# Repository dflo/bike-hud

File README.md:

# bike-hud
HUD for motorcycle helmets

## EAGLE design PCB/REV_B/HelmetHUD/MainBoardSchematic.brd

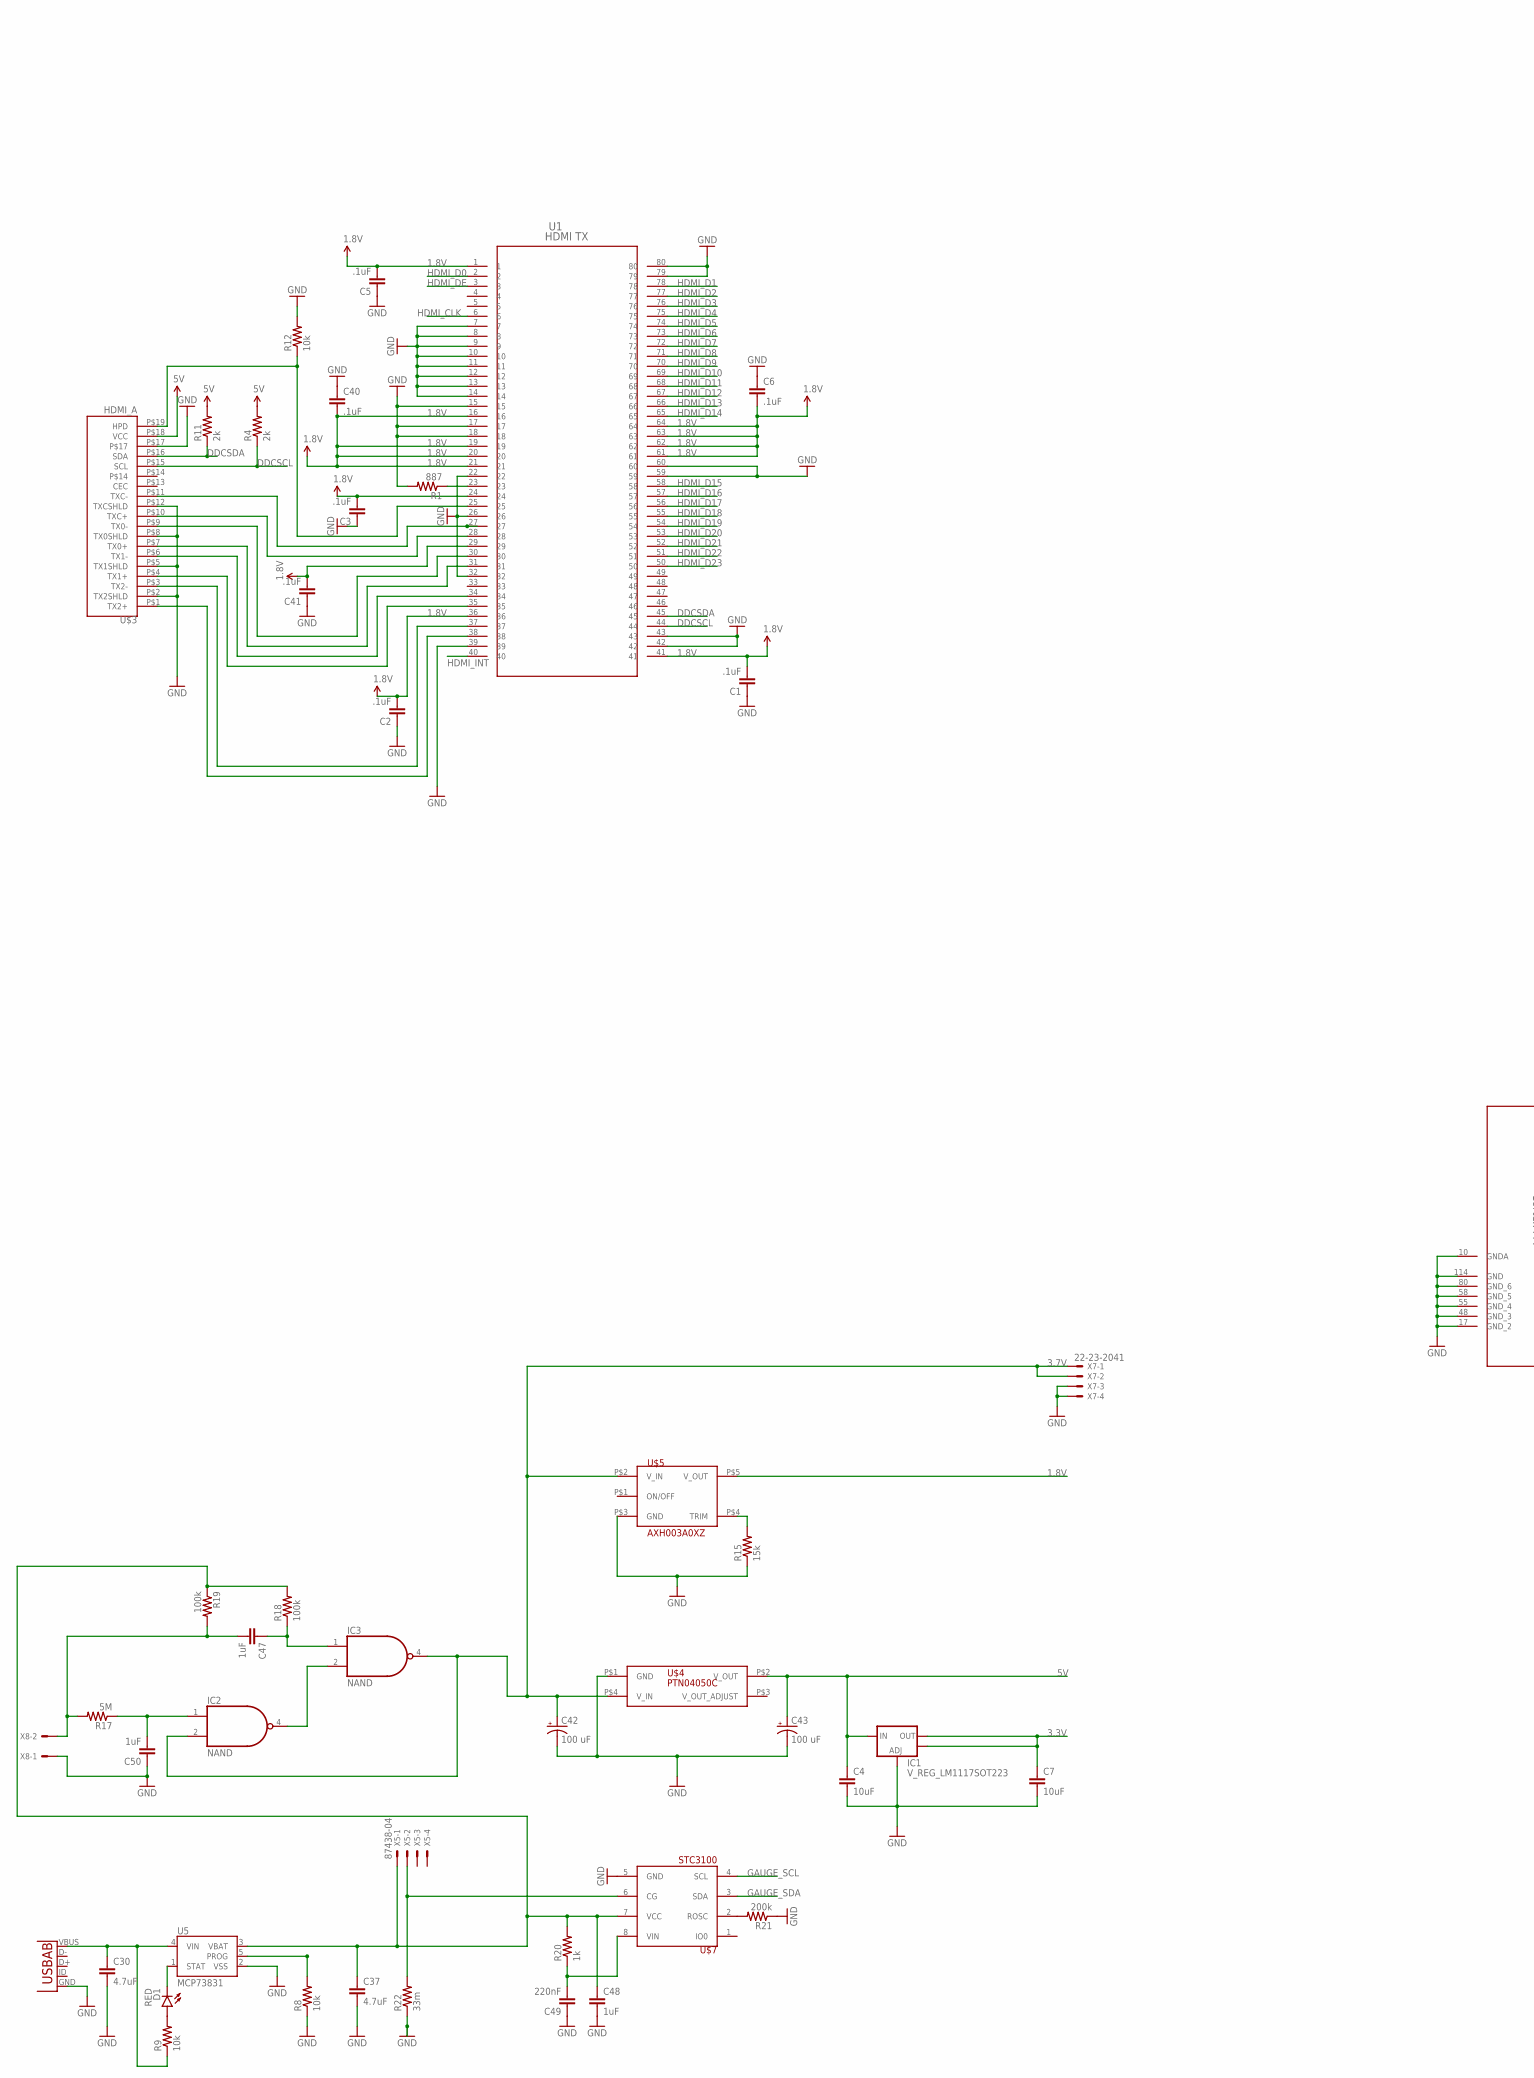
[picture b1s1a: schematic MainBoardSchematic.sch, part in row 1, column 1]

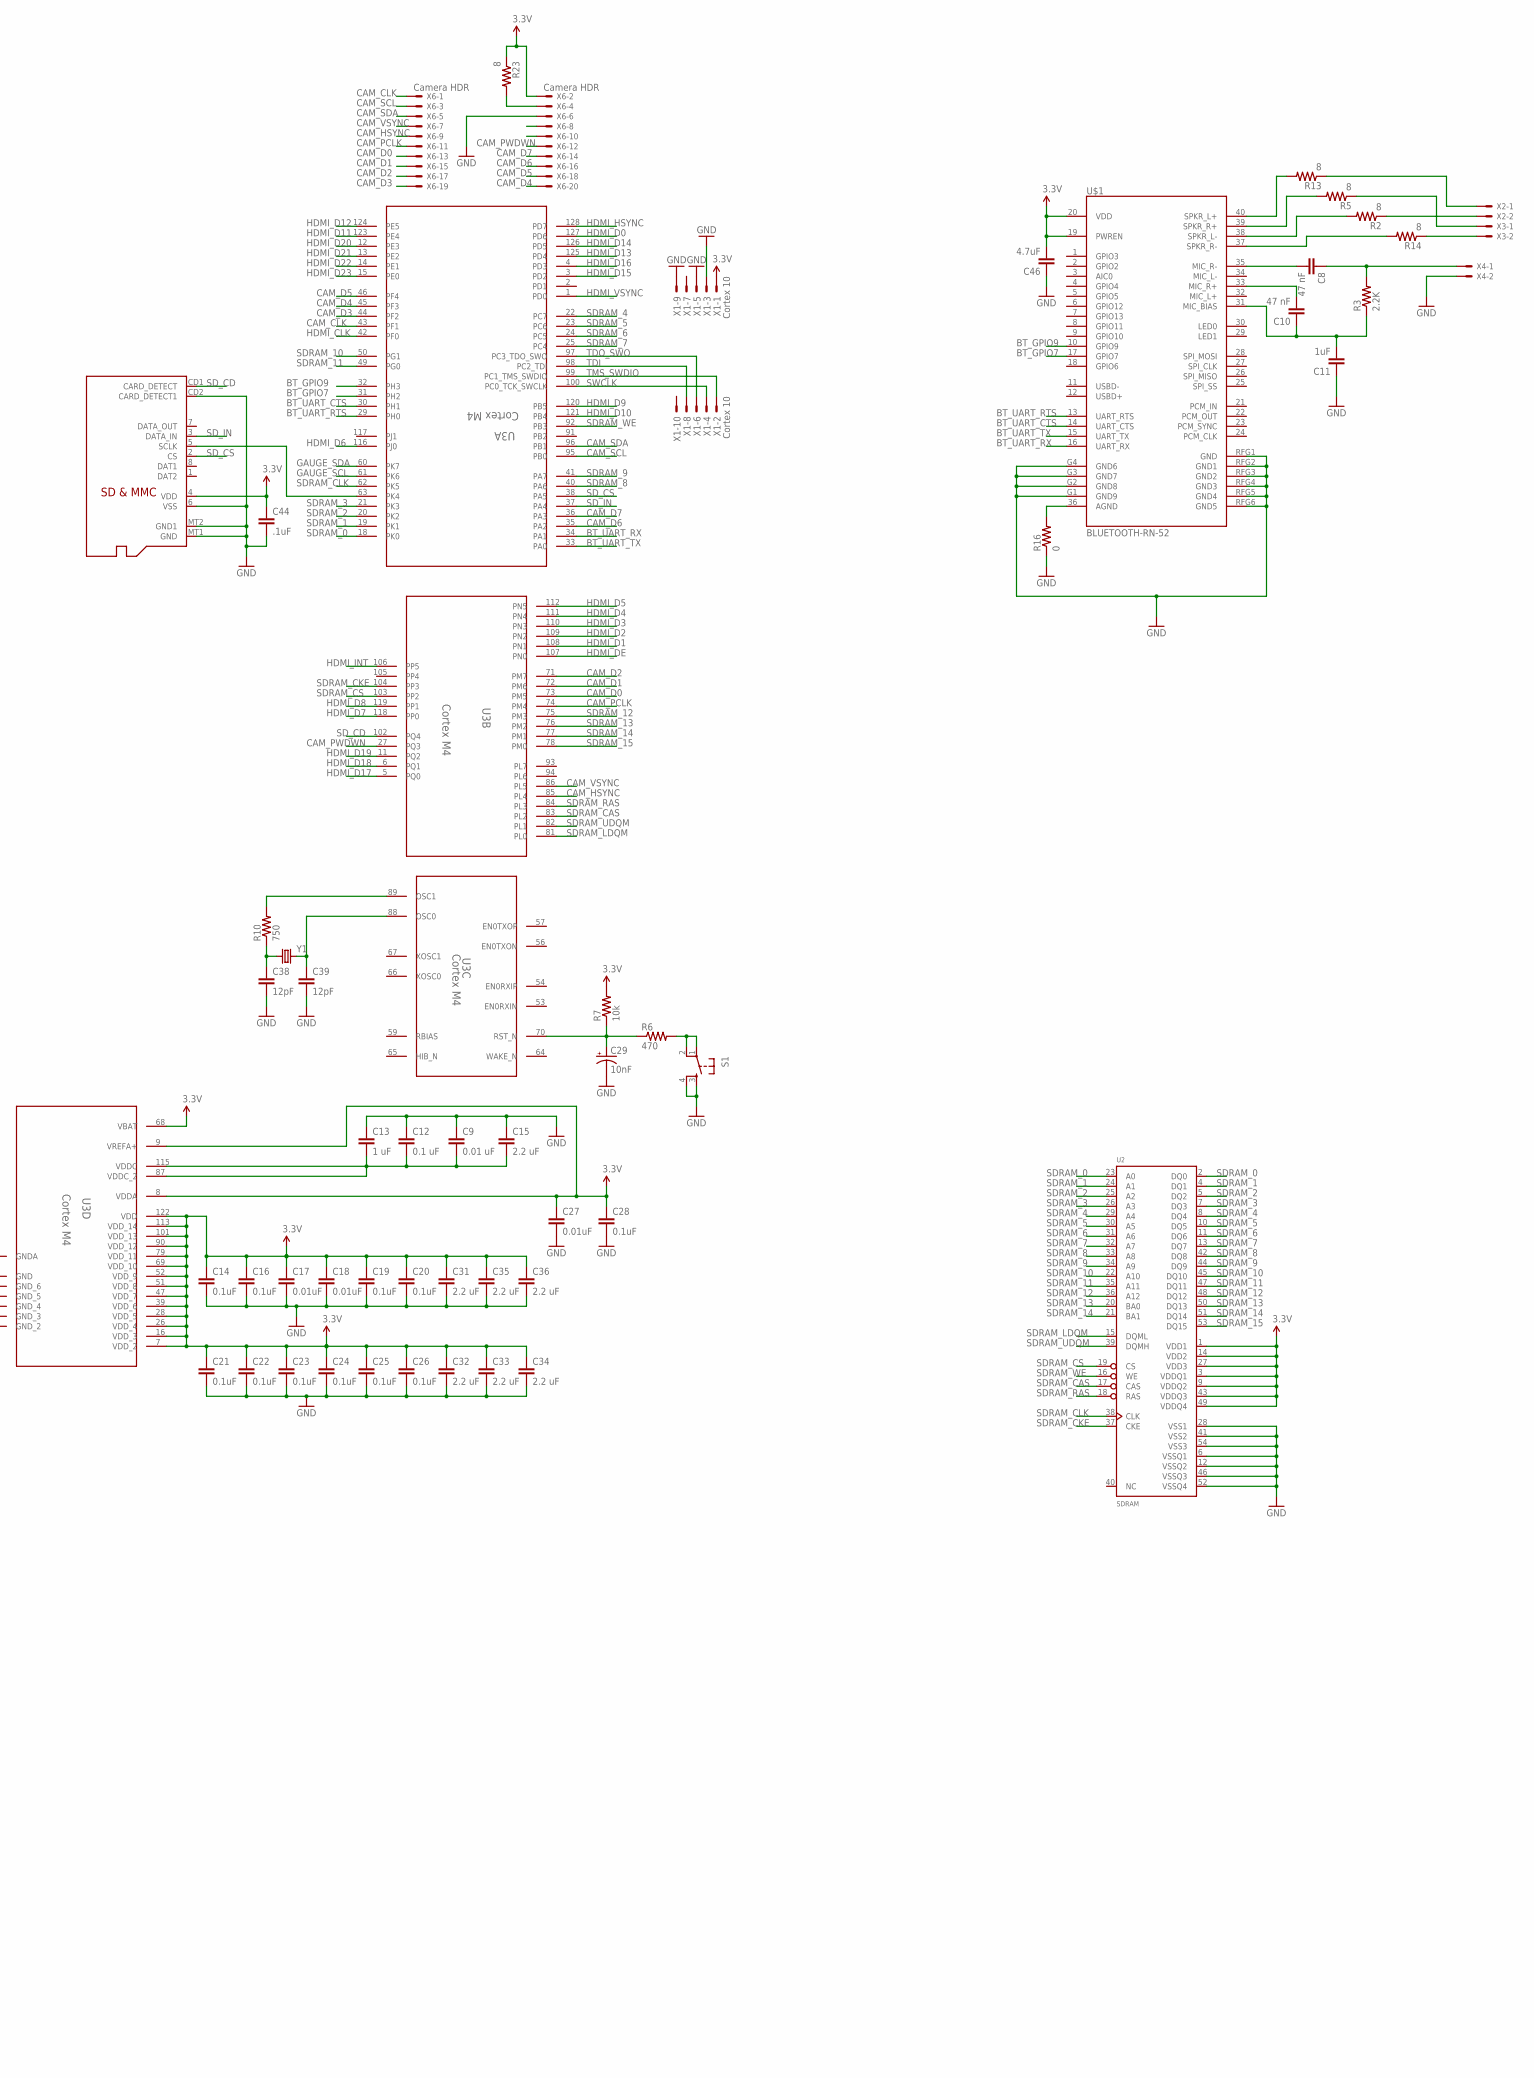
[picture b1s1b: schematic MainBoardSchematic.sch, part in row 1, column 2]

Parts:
C1, C2, C3, C5, C6, C40, C41, C44: .1uF; 0603-CAP
C4, C7: 10uF; 0603-CAP
C8, C10: 47 nF; 0603-CAP
C9: 0.01 uF; 0603-CAP
C11, C47, C48, C50: 1uF; 0603-CAP
C12: 0.1 uF; 0603-CAP
C13: 1 uF; 0603-CAP
C14, C16, C19, C20, C21, C22, C23, C24, C25, C26, C28: 0.1uF; 0603-CAP
C15, C31, C32, C33, C34, C35, C36: 2.2 uF; 0603-CAP
C17, C18, C27: 0.01uF; 0603-CAP
C29: 10nF; EIA6032
C30, C37, C46: 4.7uF; 0603-CAP
C38, C39: 12pF; 0603-CAP
C42, C43: 100 uF; EIA6032
C49: 220nF; 0603-CAP
D1: RED; LED-0603
IC1: V_REG_LM1117SOT223; SOT223
IC2, IC3: NAND; SOT23-5
R1: 887; 0603-RES
R2, R5, R13, R14, R23: 8; 1206
R3: 2.2K; 1206
R4, R11: 2k; 0603-RES
R6: 470; 0603-RES
R7, R8, R9, R12: 10k; 0603-RES
R10: 750; 0603-RES
R15: 15k; 0603-RES
R16: 0; 1206
R17: 5M; 0603-RES
R18, R19: 100k; 0603-RES
R20: 1k; 0603-RES
R21: 200k; 0603-RES
R22: 33m; 0603-RES
S1: TAC_SWITCHPTH; TACTILE-PTH
U1: HDMI TX; ST_80_2
U2: SDRAM; TSOP54-400
U3: Cortex M4; PDT0128A_N
U4: USB-AB; USB-AB-MICRO-SMD
U5: MCP73831; SOT23-5
U$1: BLUETOOTH-RN-52; RN-52
U$2: MICROSD
U$3: HDMI_A; HDMI_A_SMD
U$4: PTN04050C
U$5: AXH003A0XZ
U$7: STC3100; MSOP8
X1: Cortex 10; 1365-10
X2, X3, X4, X8: KK-156-2
X5: 87438-04
X6: Camera HDR; 87758-2016
X7: 22-23-2041
Y1: CRYSTAL; NX5032GA

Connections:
1.8V: C1.2, C2.2, C3.2, C5.2, C6.2, C40.2, C41.2, U1.1, U1.16, U1.19, U1.20, U1.21, U1.24, U1.29, U1.36, U1.41, U1.61, U1.62, U1.63, U1.64, U$5.P$5 (V_OUT)
3.3V: C7.1, C14.1, C16.1, C17.1, C18.1, C19.1, C20.1, C21.1, C22.1, C23.1, C24.1, C25.1, C26.1, C27.1, C28.1, C31.1, C32.1, C33.1, C34.1, C35.1, C36.1, C44.1, C46.2, IC1.2 (OUT), IC1.4 (OUT), R7.2, R23.1, U2.1 (VDD1), U2.3 (VDDQ1), U2.9 (VDDQ2), U2.14 (VDD2), U2.27 (VDD3), U2.43 (VDDQ3), U2.49 (VDDQ4), U3.7 (VDD_2), U3.8 (VDDA), U3.9 (VREFA+), U3.16 (VDD_3), U3.26 (VDD_4), U3.28 (VDD_5), U3.39 (VDD_6), U3.47 (VDD_7), U3.51 (VDD_8), U3.52 (VDD_9), U3.68 (VBAT), U3.69 (VDD_10), U3.79 (VDD_11), U3.90 (VDD_12), U3.101 (VDD_13), U3.113 (VDD_14), U3.122 (VDD), U$1.19 (PWREN), U$1.20 (VDD), U$2.4 (VDD), X1.1, X6.2
3.7V: C42.P$1 (+), IC2.2 (I1), IC3.4 (O), U$4.P$4 (V_IN), U$5.P$2 (V_IN), X7.1, X7.2
5V: C4.1, C43.P$1 (+), IC1.3 (IN), R4.2, R11.2, U$3.P$18 (VCC), U$4.P$2 (V_OUT)
BT_GPIO7: U3.31 (PH2), U$1.17 (GPIO7)
BT_GPIO9: U3.32 (PH3), U$1.10 (GPIO9)
BT_UART_CTS: U3.30 (PH1), U$1.14 (UART_CTS)
BT_UART_RTS: U3.29 (PH0), U$1.13 (UART_RTS)
BT_UART_RX: U3.34 (PA1), U$1.16 (UART_RX)
BT_UART_TX: U3.33 (PA0), U$1.15 (UART_TX)
CAM_CLK: U3.43 (PF1), X6.1
CAM_D0: U3.73 (PM5), X6.13
CAM_D1: U3.72 (PM6), X6.15
CAM_D2: U3.71 (PM7), X6.17
CAM_D3: U3.44 (PF2), X6.19
CAM_D4: U3.45 (PF3), X6.20
CAM_D5: U3.46 (PF4), X6.18
CAM_D6: U3.35 (PA2), X6.16
CAM_D7: U3.36 (PA3), X6.14
CAM_HSYNC: U3.85 (PL4), X6.9
CAM_PCLK: U3.74 (PM4), X6.11
CAM_PWDWN: U3.27 (PQ3), X6.12
CAM_SCL: U3.95 (PB0), X6.3
CAM_SDA: U3.96 (PB1), X6.5
CAM_VSYNC: U3.86 (PL5), X6.7
DDCSCL: R4.1, U1.44, U$3.P$15 (SCL)
DDCSDA: R11.1, U1.45, U$3.P$16 (SDA)
GAUGE_SCL: U3.61 (PK6), U$7.4 (SCL)
GAUGE_SDA: U3.60 (PK7), U$7.3 (SDA)
GND: C1.1, C2.1, C3.1, C4.2, C5.1, C6.1, C7.2, C9.1, C11.1, C12.1, C13.1, C14.2, C15.1, C16.2, C17.2, C18.2, C19.2, C20.2, C21.2, C22.2, C23.2, C24.2, C25.2, C26.2, C27.2, C28.2, C29.P$2 (-), C30.2, C31.2, C32.2, C33.2, C34.2, C35.2, C36.2, C37.2, C38.2, C39.2, C40.1, C41.1, C42.P$2 (-), C43.P$2 (-), C44.2, C46.1, C48.2, C49.1, C50.1, IC1.1 (ADJ), IC2.3 (GND), IC3.3 (GND), R1.2, R8.1, R12.2, R15.1, R16.1, R21.1, R22.1, S1.3, S1.4, U1.7, U1.8, U1.9, U1.10, U1.11, U1.12, U1.13, U1.14, U1.15, U1.17, U1.18, U1.22, U1.26, U1.32, U1.39, U1.42, U1.43, U1.59, U1.60, U1.79, U1.80, U2.6 (VSSQ1), U2.12 (VSSQ2), U2.28 (VSS1), U2.41 (VSS2), U2.46 (VSSQ3), U2.52 (VSSQ4), U2.54 (VSS3), U3.10 (GNDA), U3.17 (GND_2), U3.48 (GND_3), U3.55 (GND_4), U3.58 (GND_5), U3.80 (GND_6), U3.114 (GND), U4.GND, U5.2 (VSS), U$1.G1 (GND9), U$1.G2 (GND8), U$1.G3 (GND7), U$1.G4 (GND6), U$1.RFG1 (GND), U$1.RFG2 (GND1), U$1.RFG3 (GND2), U$1.RFG4 (GND3), U$1.RFG5 (GND4), U$1.RFG6 (GND5), U$2.6 (VSS), U$2.CD2 (CARD_DETECT1), U$2.MT1 (GND), U$2.MT2 (GND1), U$3.P$2 (TX2SHLD), U$3.P$5 (TX1SHLD), U$3.P$8 (TX0SHLD), U$3.P$12 (TXCSHLD), U$3.P$17, U$4.P$1 (GND), U$5.P$3 (GND), U$7.5 (GND), X1.3, X1.5, X1.9, X4.2, X6.6, X7.3, X7.4, X8.1
HDMI_CLK: U1.6, U3.42 (PF0)
HDMI_D0: U1.2, U3.127 (PD6)
HDMI_D1: U1.78, U3.108 (PN1)
HDMI_D2: U1.77, U3.109 (PN2)
HDMI_D3: U1.76, U3.110 (PN3)
HDMI_D4: U1.75, U3.111 (PN4)
HDMI_D5: U1.74, U3.112 (PN5)
HDMI_D6: U1.73, U3.116 (PJ0)
HDMI_D7: U1.72, U3.118 (PP0)
HDMI_D8: U1.71, U3.119 (PP1)
HDMI_D9: U1.70, U3.120 (PB5)
HDMI_D10: U1.69, U3.121 (PB4)
HDMI_D11: U1.68, U3.123 (PE4)
HDMI_D12: U1.67, U3.124 (PE5)
HDMI_D13: U1.66, U3.125 (PD4)
HDMI_D14: U1.65, U3.126 (PD5)
HDMI_D15: U1.58, U3.3 (PD2)
HDMI_D16: U1.57, U3.4 (PD3)
HDMI_D17: U1.56, U3.5 (PQ0)
HDMI_D18: U1.55, U3.6 (PQ1)
HDMI_D19: U1.54, U3.11 (PQ2)
HDMI_D20: U1.53, U3.12 (PE3)
HDMI_D21: U1.52, U3.13 (PE2)
HDMI_D22: U1.51, U3.14 (PE1)
HDMI_D23: U1.50, U3.15 (PE0)
HDMI_DE: U1.3, U3.107 (PN0)
HDMI_HSYNC: U3.128 (PD7)
HDMI_INT: U1.40, U3.106 (PP5)
HDMI_VSYNC: U3.1 (PD0)
unnamed: R12.1, U1.25, U$3.P$19 (HPD)
unnamed: R1.1, U1.23
unnamed: U1.34, U$3.P$6 (TX1-)
unnamed: U1.30, U$3.P$9 (TX0-)
unnamed: U1.31, U$3.P$7 (TX0+)
unnamed: U1.35, U$3.P$4 (TX1+)
unnamed: U1.37, U$3.P$3 (TX2-)
unnamed: U1.38, U$3.P$1 (TX2+)
unnamed: U1.28, U$3.P$10 (TXC+)
unnamed: C8.2, U$1.35 (MIC_R-)
unnamed: C10.1, C11.2, R3.1, U$1.31 (MIC_BIAS)
unnamed: C8.1, R3.2, X4.1
unnamed: R6.2, S1.1, S1.2
unnamed: R13.2, U$1.40 (SPKR_L+)
unnamed: R5.2, U$1.39 (SPKR_R+)
unnamed: R2.2, U$1.38 (SPKR_L-)
unnamed: R14.2, U$1.37 (SPKR_R-)
unnamed: R23.2, X6.4
unnamed: U1.27, U$3.P$11 (TXC-)
unnamed: C30.1, R9.1, U4.VBUS, U5.4 (VIN)
unnamed: R15.2, U$5.P$4 (TRIM)
unnamed: C9.2, C12.2, C13.2, C15.2, U3.87 (VDDC_2), U3.115 (VDDC)
unnamed: C29.P$1 (+), R6.1, R7.1, U3.70 (RST_N)
unnamed: C38.1, R10.1, Y1.P$1 (1)
unnamed: R8.2, U5.5 (PROG)
unnamed: C39.1, U3.88 (OSC0), Y1.P$2 (2)
unnamed: R16.2, U$1.36 (AGND)
unnamed: R10.2, U3.89 (OSC1)
unnamed: R14.1, X3.2
unnamed: R2.1, X2.2
unnamed: R5.1, X3.1
unnamed: R13.1, X2.1
unnamed: D1.A, R9.2
unnamed: D1.C, U5.1 (STAT)
unnamed: IC2.4 (O), IC3.2 (I1)
unnamed: C47.1, IC3.1 (I0), R18.1
unnamed: C47.2, R17.2, R19.2, X8.2
unnamed: C37.1, C48.1, R18.2, R19.1, R20.2, U5.3 (VBAT), U$7.7 (VCC), X5.1
unnamed: C50.2, IC2.1 (I0), R17.1
unnamed: C49.2, R20.1, U$7.8 (VIN)
unnamed: R21.2, U$7.2 (ROSC)
unnamed: R22.2, U$7.6 (CG), X5.2
unnamed: U3.63 (PK4), U$2.5 (SCLK)
unnamed: C10.2, U$1.33 (MIC_R+)
SDRAM_0: U2.2 (DQ0), U2.23 (A0), U3.18 (PK0)
SDRAM_1: U2.4 (DQ1), U2.24 (A1), U3.19 (PK1)
SDRAM_2: U2.5 (DQ2), U2.25 (A2), U3.20 (PK2)
SDRAM_3: U2.7 (DQ3), U2.26 (A3), U3.21 (PK3)
SDRAM_4: U2.8 (DQ4), U2.29 (A4), U3.22 (PC7)
SDRAM_5: U2.10 (DQ5), U2.30 (A5), U3.23 (PC6)
SDRAM_6: U2.11 (DQ6), U2.31 (A6), U3.24 (PC5)
SDRAM_7: U2.13 (DQ7), U2.32 (A7), U3.25 (PC4)
SDRAM_8: U2.33 (A8), U2.42 (DQ8), U3.40 (PA6)
SDRAM_9: U2.34 (A9), U2.44 (DQ9), U3.41 (PA7)
SDRAM_10: U2.22 (A10), U2.45 (DQ10), U3.50 (PG1)
SDRAM_11: U2.35 (A11), U2.47 (DQ11), U3.49 (PG0)
SDRAM_12: U2.36 (A12), U2.48 (DQ12), U3.75 (PM3)
SDRAM_13: U2.20 (BA0), U2.50 (DQ13), U3.76 (PM2)
SDRAM_14: U2.21 (BA1), U2.51 (DQ14), U3.77 (PM1)
SDRAM_15: U2.53 (DQ15), U3.78 (PM0)
SDRAM_CAS: U2.17 (CAS), U3.83 (PL2)
SDRAM_CKE: U2.37 (CKE), U3.104 (PP3)
SDRAM_CLK: U2.38 (CLK), U3.62 (PK5)
SDRAM_CS: U2.19 (CS), U3.103 (PP2)
SDRAM_LDQM: U2.15 (DQML), U3.81 (PL0)
SDRAM_RAS: U2.18 (RAS), U3.84 (PL3)
SDRAM_UDQM: U2.39 (DQMH), U3.82 (PL1)
SDRAM_WE: U2.16 (WE), U3.92 (PB3)
SD_CD: U3.102 (PQ4), U$2.CD1 (CARD_DETECT)
SD_CS: U3.38 (PA5), U$2.2 (CS)
SD_IN: U3.37 (PA4), U$2.3 (DATA_IN)
SWCLK: U3.100 (PC0_TCK_SWCLK), X1.4
TDI: U3.98 (PC2_TDI), X1.8
TDO_SWO: U3.97 (PC3_TDO_SWO), X1.6
TMS_SWDIO: U3.99 (PC1_TMS_SWDIO), X1.2
VCC: IC2.5 (VCC), IC3.5 (VCC)

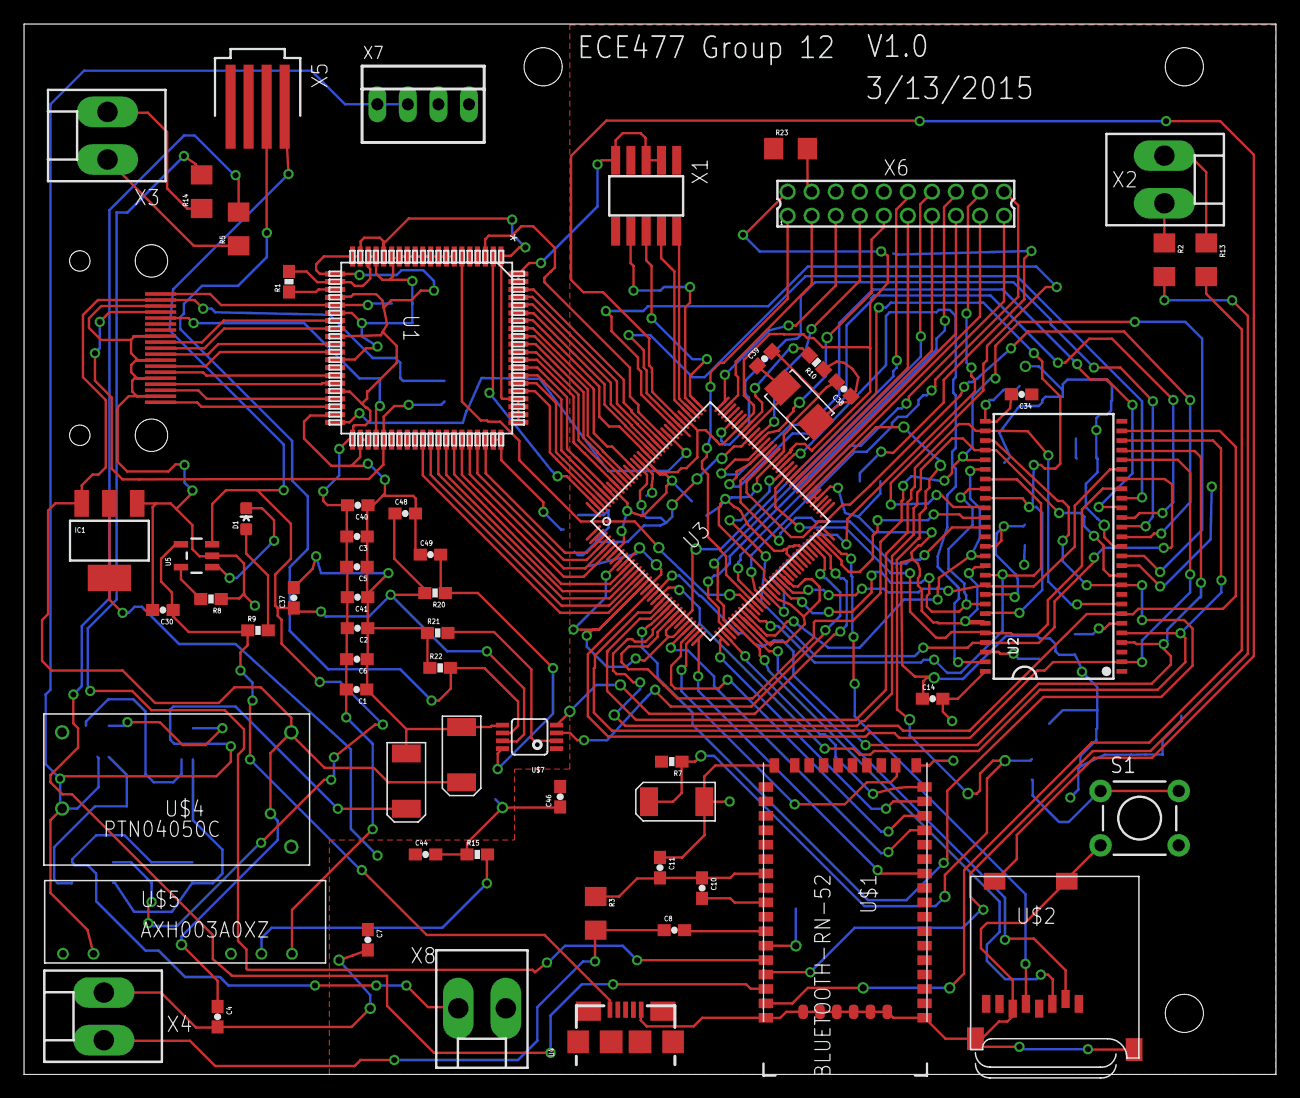
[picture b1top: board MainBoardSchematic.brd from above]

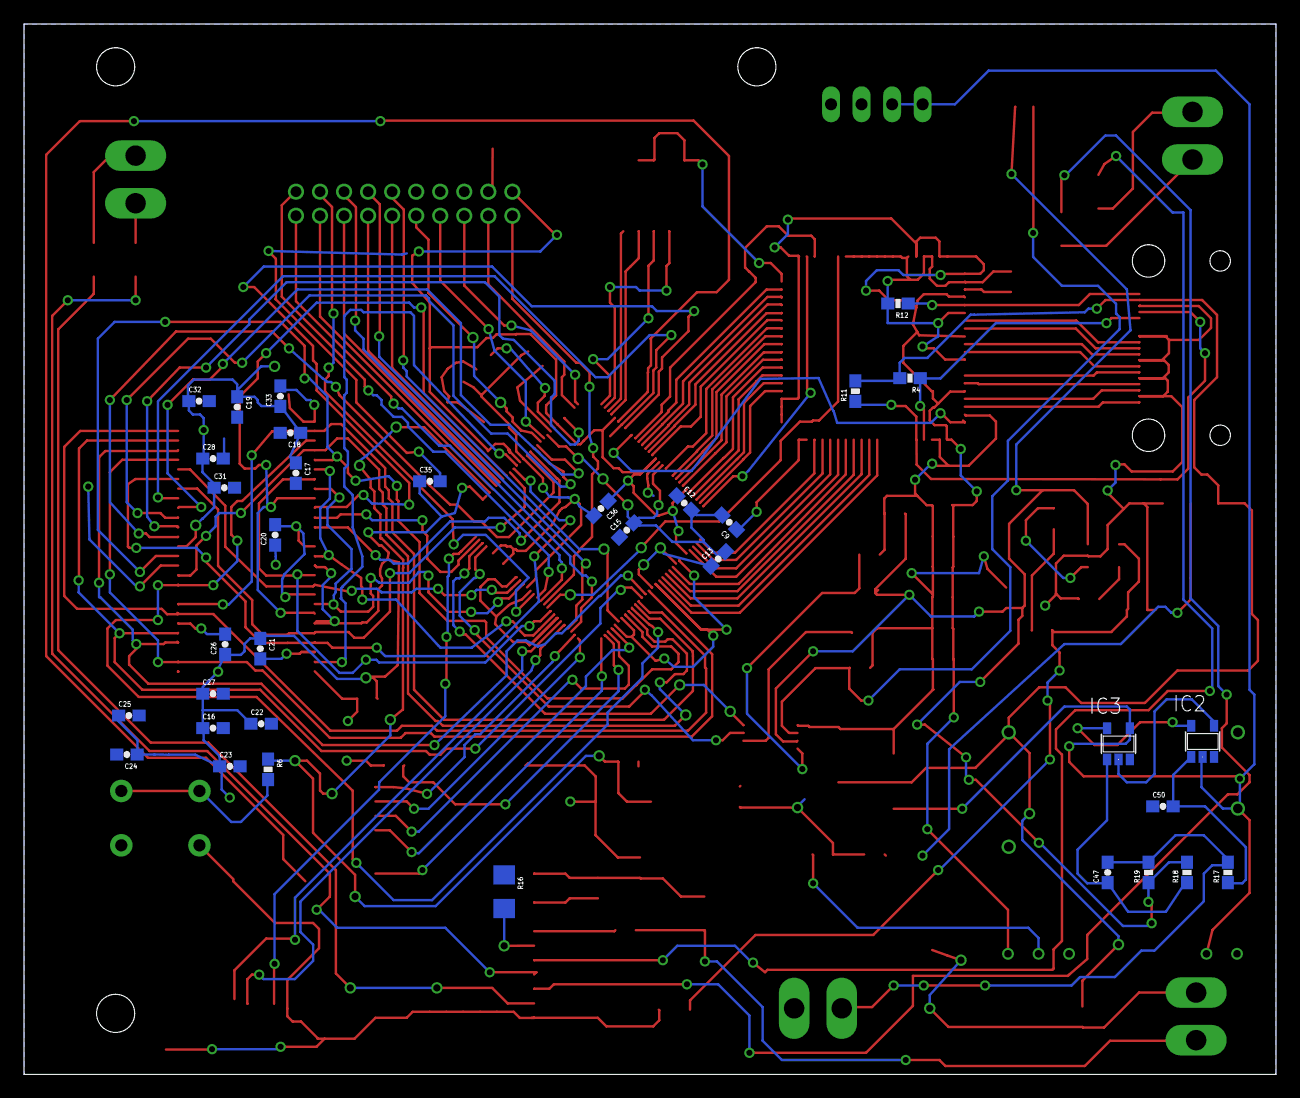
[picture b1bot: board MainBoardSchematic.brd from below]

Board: 2 copper layers, 104.1 x 87.4 mm, 97 parts (34 on the bottom side), 133 nets.

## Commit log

2015-02-11 dir setup
2015-02-11 dir setup 2
2015-02-23 Parts Library V1
2015-02-24 Schematic V1
2015-02-25 pocketsphinx demo
2015-02-25 Schematic V2
2015-03-03 Schematic V3
2015-03-05 Schematic V4
2015-03-11 PCB REV B
2015-03-13 PCB REV B update
2015-03-22 Got rid of the mac ds store thing
2015-03-22 init for embedded
2015-03-24 Add the latest PCB
2015-03-30 With PWM
2015-03-30 UART
2015-03-31 Corrected workspace directory
2015-03-31 ignore stuff fixed. otherwise would mess up settings at every sync
2015-04-01 UART v1
2015-04-01 UART Completed
2015-04-02 Switched UART to Ports K0-K3 on dev board
2015-04-08 SD card init is on the way with working SPI
2015-04-15 mjpeg
2015-04-17 camera
2015-04-17 sdc change
2015-04-21 prelim bluetooth, voice, gps speed. needs testing
2015-04-21 app clean up
2015-04-25 trying to implement services
2015-04-27 Weather now working
2015-05-06 this should be it
2015-05-07 updating app, close to done
2015-05-07 commit to get the test app onto github so i can test from my laptop and not have to go home

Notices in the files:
parts and their libraries:
SparkFun-Capacitors: Licensing: Creative Commons ShareAlike 4.0 International - https://creativecommons.org/licenses/by-sa/4.0
